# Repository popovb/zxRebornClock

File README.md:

# ИНСТРУКЦИЯ ПО СБОРКЕ И ЗАПУСКУ

## Повышайка на 200 В

Запаиваем следующие элементы: `J1, U3, C8, R55, C9, L1, D8, C11, D7, Q12, R56, Q11, C10, R57, R58`.
Подключаем 12 В. На С11 долно быть около 200 В. Если есть, переходим к следующему шагу.

## Понижайка на 3.3 В

Запаиваем следующие элементы: `D6, C2, U2, C4, C5, R1, D1`. Подключаем 12 В. На C4 должно быть
3.3 В и горит D1. Если есть, переходим к следующему шагу.

## Микроконтроллер

Запаиваем: `U1, C1, J2, U4, R12-R15, D2-D5, Sw2-Sw6, R29-R33, R53, R54, J4`.

Идём сюда https://github.com/ch32-rs/wchisp/releases/tag/v0.3.0 и берём прошиватор
под нужную платформу. Как минимум работает в Debian и Windows 10.

Плата обесточена. Зажимаем кнопку Download, подрубаем usb кабель к компу, отпускаем кнопку и
у нас несколько секунд, чтобы запустить прошиватор.

Для начала можно дать команду вывода информации чипа: `wchisp info`.

Если заработало, то можно прошить `blink.hex` из раздела релизов. Команда `wchisp flash blink.hex`. Будут
мигать светодиоды D2-D5.

Если всё работает -- прошиваем боевую прошивку: `zxRebornClock.hex`.

## Конфигурирование

Питание 12 В и USB выключены. Зажимаем кнопку F и подаём питание 12 В. Загорается зелёный
светодиод -- контроллер перешёл в режим конфигурирования.

Подключаем к J4 USB-Uart переходник и подключаем его к компьютеру.

Из раздела релизов берём программу конфигуратор `zxrc_configurator.win64.exe` или
`zxrc_configurator_lin64` (проверял в Windows 10 и Debian). Запускаем,
выбираем ком-порт и отвечаем на вопросы. В конце будет выдано подтверждение успеха
конфигурирования.

## Дальше

Запаиваем всё остальное. Должно всё заработать.

## Если не заработало?

Тогда идём сюда и спрашиваем https://t.me/zxRebornClock

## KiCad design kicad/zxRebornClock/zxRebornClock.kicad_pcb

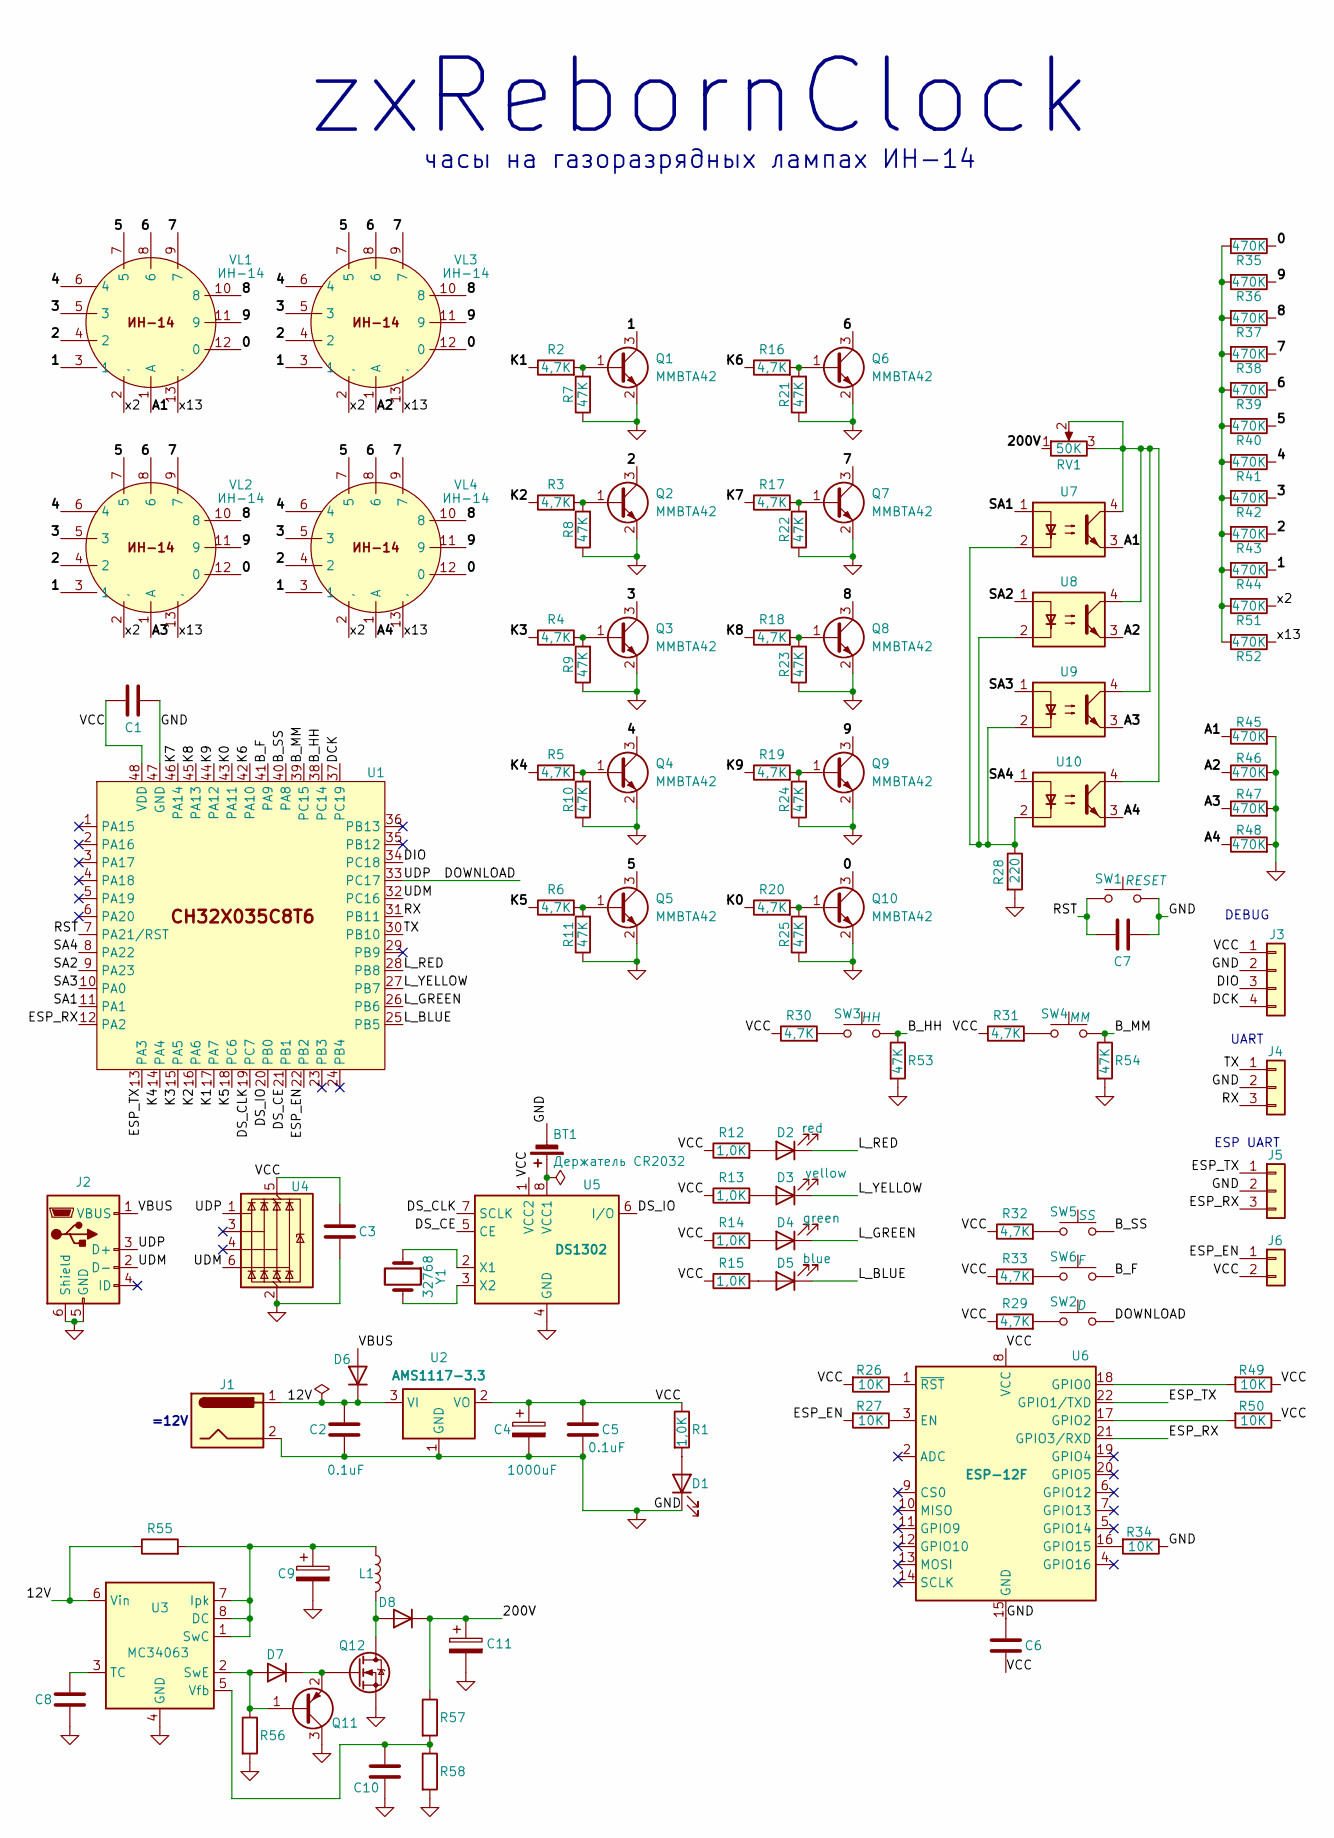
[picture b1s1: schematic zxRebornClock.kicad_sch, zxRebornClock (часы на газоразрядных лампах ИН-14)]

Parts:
BT1: Держатель CR2032; BatteryHolder_MYOUNG_BS-07-A1BJ001_CR2032
C1, C3, C6, C7: 0,1uF; C_0805_2012Metric_Pad1.18x1.45mm_HandSolder
C2, C5: 0.1uF; C_0805_2012Metric_Pad1.18x1.45mm_HandSolder
C4: 1000uF; CP_Radial_D8.0mm_P3.50mm
C8: 2200pF; C_0805_2012Metric_Pad1.18x1.45mm_HandSolder
C9: 220uF; CP_Radial_D6.3mm_P2.50mm
C10: 0.01uF; C_0805_2012Metric_Pad1.18x1.45mm_HandSolder
C11: 2.2uF; CP_Radial_D6.3mm_P2.50mm
D1: white; LED_0805_2012Metric_Pad1.15x1.40mm_HandSolder
D2: red; LED_0805_2012Metric_Pad1.15x1.40mm_HandSolder
D3: yellow; LED_0805_2012Metric_Pad1.15x1.40mm_HandSolder
D4: green; LED_0805_2012Metric_Pad1.15x1.40mm_HandSolder
D5: blue; LED_0805_2012Metric_Pad1.15x1.40mm_HandSolder
D6, D8: US1G; D_SMA
D7: LL4148; D_MiniMELF
J1: Jack DC; BarrelJack_Horizontal
J2: MicroUSB type B розетка; USB_Micro-B_Molex-105017-0001
J3: Гребёнка 1x4x2.54; PinHeader_1x04_P2.54mm_Vertical
J4, J5: Гребёнка 1x3x2.54; PinHeader_1x03_P2.54mm_Vertical
J6: Гребёнка 1x2x2.54; PinHeader_1x02_P2.54mm_Vertical
L1: 100uH; L_D8mm_P3mm
Q1, Q2, Q3, Q4, Q5, Q6, Q7, Q8, Q9, Q10: MMBTA42; SOT-23
Q11: MMBTA56; SOT-23
Q12: IRF740; TO-220-3_Vertical
R1, R12, R13, R14, R15: 1,0K; R_0805_2012Metric_Pad1.20x1.40mm_HandSolder
R2, R3, R4, R5, R6, R16, R17, R18, R19, R20, R29, R30, R31, R32, R33: 4,7K; R_0805_2012Metric_Pad1.20x1.40mm_HandSolder
R7, R8, R9, R10, R11, R21, R22, R23, R24, R25, R53, R54: 47K; R_0805_2012Metric_Pad1.20x1.40mm_HandSolder
R26, R27, R34, R49, R50: 10K; R_0805_2012Metric_Pad1.20x1.40mm_HandSolder
R28: 220; R_0805_2012Metric_Pad1.20x1.40mm_HandSolder
R35, R36, R37, R38, R39, R40, R41, R42, R43, R44, R45, R46, R47, R48, R51, R52: 470K; R_0805_2012Metric_Pad1.20x1.40mm_HandSolder
R55: 0.33; R_0805_2012Metric_Pad1.20x1.40mm_HandSolder
R56: 1K; R_0805_2012Metric_Pad1.20x1.40mm_HandSolder
R57: 470K 1%; R_Axial_DIN0207_L6.3mm_D2.5mm_P7.62mm_Horizontal
R58: 3K 1%; R_Axial_DIN0207_L6.3mm_D2.5mm_P7.62mm_Horizontal
RV1: 50K; TRIM_3362P-1-103
SW1: RESET; SW_SPST_CK_RS282G05A3
SW2: D; SW_SPST_CK_RS282G05A3
SW3: HH; SW_PUSH_6mm_H9.5mm
SW4: MM; SW_PUSH_6mm_H9.5mm
SW5: SS; SW_PUSH_6mm_H9.5mm
SW6: F; SW_PUSH_6mm_H9.5mm
U1: CH32X035C8T6; LQFP-48_7x7mm_P0.5mm
U2: AMS1117-3.3; SOT-223-3_TabPin2
U3: MC34063; SOIC-8_3.9x4.9mm_P1.27mm
U4: USBLC6-4SC6; SOT-23-6
U5: DS1302; SO-8_3.9x4.9mm_P1.27mm
U6: ESP-12F; ESP-12E
U7, U8, U9, U10: TLP627; DIP-4_W7.62mm
VL1, VL2, VL3, VL4: ИН-14
Y1: 32768; Crystal_C38-LF_D3.0mm_L8.0mm_Horizontal

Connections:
/0: Q10.3 (C), R35.1, VL1.12 (0), VL2.12 (0), VL3.12 (0), VL4.12 (0)
/1: Q1.3 (C), R44.1, VL1.3 (1), VL2.3 (1), VL3.3 (1), VL4.3 (1)
/2: Q2.3 (C), R43.1, VL1.4 (2), VL2.4 (2), VL3.4 (2), VL4.4 (2)
/3: Q3.3 (C), R42.1, VL1.5 (3), VL2.5 (3), VL3.5 (3), VL4.5 (3)
/4: Q4.3 (C), R41.1, VL1.6 (4), VL2.6 (4), VL3.6 (4), VL4.6 (4)
/5: Q5.3 (C), R40.1, VL1.7 (5), VL2.7 (5), VL3.7 (5), VL4.7 (5)
/6: Q6.3 (C), R39.1, VL1.8 (6), VL2.8 (6), VL3.8 (6), VL4.8 (6)
/7: Q7.3 (C), R38.1, VL1.9 (7), VL2.9 (7), VL3.9 (7), VL4.9 (7)
/8: Q8.3 (C), R37.1, VL1.10 (8), VL2.10 (8), VL3.10 (8), VL4.10 (8)
/9: Q9.3 (C), R36.1, VL1.11 (9), VL2.11 (9), VL3.11 (9), VL4.11 (9)
/12V: C2.1, D6.1 (K), J1.1, R55.1, U2.3 (VI), U3.6 (Vin)
/200V: C11.1, D8.1 (K), R57.1, RV1.1
/A1: R45.1, U7.3, VL1.1 (A)
/A2: R46.1, U8.3, VL3.1 (A)
/A3: R47.1, U9.3, VL2.1 (A)
/A4: R48.1, U10.3, VL4.1 (A)
/B_F: SW6.2, U1.41 (PA9)
/B_HH: R53.1, SW3.2, U1.38 (PC14)
/B_MM: R54.1, SW4.2, U1.39 (PC15)
/B_SS: SW5.2, U1.40 (PA8)
/DCK: J3.4, U1.37 (PC19)
/DIO: J3.3, U1.34 (PC18)
/DOWNLOAD: J2.3 (D+), SW2.2, U1.33 (PC17), U4.1 (I/O1)
/DS_CE: U1.21 (PB1), U5.5 (CE)
/DS_CLK: U1.19 (PC7), U5.7 (SCLK)
/DS_IO: U1.20 (PB0), U5.6 (I/O)
/ESP_EN: J6.1, R27.2, U1.22 (PB2)
/ESP_RX: J5.3, U1.12 (PA2), U6.21 (GPIO3/RXD)
/ESP_TX: J5.1, U1.13 (PA3), U6.22 (GPIO1/TXD)
/K0: R20.1, U1.43 (PA11)
/K1: R2.1, U1.17 (PA7)
/K2: R3.1, U1.16 (PA6)
/K3: R4.1, U1.15 (PA5)
/K4: R5.1, U1.14 (PA4)
/K5: R6.1, U1.18 (PC6)
/K6: R16.1, U1.42 (PA10)
/K7: R17.1, U1.46 (PA14)
/K8: R18.1, U1.45 (PA13)
/K9: R19.1, U1.44 (PA12)
/L_BLUE: D5.1 (K), U1.25 (PB5)
/L_GREEN: D4.1 (K), U1.26 (PB6)
/L_RED: D2.1 (K), U1.28 (PB8)
/L_YELLOW: D3.1 (K), U1.27 (PB7)
/RST: C7.1, SW1.1, U1.7 (PA21/RST)
/RX: J4.3, U1.31 (PB11)
/SA1: U1.11 (PA1), U7.1
/SA2: U1.9 (PA23), U8.1
/SA3: U1.10 (PA0), U9.1
/SA4: U1.8 (PA22), U10.1
/TX: J4.1, U1.30 (PB10)
/UDM: J2.2 (D-), U1.32 (PC16), U4.6 (I/O4)
/VBUS: D6.2 (A), J2.1 (VBUS)
/VCC: C1.2, C3.1, C4.1, C5.1, C6.2, J3.1, J6.2, R1.1, R12.1, R13.1, R14.1, R15.1, R26.2, R29.1, R30.1, R31.1, R32.1, R33.1, R49.1, R50.1, U1.48 (VDD), U2.2 (VO), U4.5 (VBUS), U5.1 (VCC2), U6.8 (VCC)
/x2: R51.1, VL1.2 (,), VL2.2 (,), VL3.2 (,), VL4.2 (,)
/x13: R52.1, VL1.13 (,), VL2.13 (,), VL3.13 (,), VL4.13 (,)
GND: BT1.2 (-), C1.1, C2.2, C3.2, C4.2, C5.2, C6.1, C7.2, C8.2, C9.2, C10.2, C11.2, D1.1 (K), J1.2, J2.5 (GND), J2.6 (Shield), J3.2, J4.2, J5.2, Q1.2 (E), Q2.2 (E), Q3.2 (E), Q4.2 (E), Q5.2 (E), Q6.2 (E), Q7.2 (E), Q8.2 (E), Q9.2 (E), Q10.2 (E), Q11.3 (C), Q12.3 (S), R7.1, R8.1, R9.1, R10.1, R11.1, R21.1, R22.1, R23.1, R24.1, R25.1, R28.2, R34.1, R45.2, R46.2, R47.2, R48.2, R53.2, R54.2, R56.2, R58.2, SW1.2, U1.47 (GND), U2.1 (GND), U3.4 (GND), U4.2 (GND), U5.4 (GND), U6.15 (GND)
unnamed: BT1.1 (+), U5.8 (VCC1)
unnamed: D1.2 (A), R1.2
unnamed: D2.2 (A), R12.2
unnamed: D3.2 (A), R13.2
unnamed: D4.2 (A), R14.2
unnamed: D5.2 (A), R15.2
unnamed: D7.2 (A), Q11.1 (B), R56.1, U3.2 (SwE)
unnamed: D7.1 (K), Q11.2 (E), Q12.1 (G)
unnamed: D8.2 (A), L1.2, Q12.2 (D)
unnamed: Q1.1 (B), R2.2, R7.2
unnamed: Q2.1 (B), R3.2, R8.2
unnamed: Q3.1 (B), R4.2, R9.2
unnamed: Q4.1 (B), R5.2, R10.2
unnamed: Q5.1 (B), R6.2, R11.2
unnamed: Q6.1 (B), R16.2, R21.2
unnamed: Q7.1 (B), R17.2, R22.2
unnamed: Q8.1 (B), R18.2, R23.2
unnamed: Q9.1 (B), R19.2, R24.2
unnamed: Q10.1 (B), R20.2, R25.2
unnamed: R28.1, U7.2, U8.2, U9.2, U10.2
unnamed: R29.2, SW2.1
unnamed: R30.2, SW3.1
unnamed: R31.2, SW4.1
unnamed: R32.2, SW5.1
unnamed: R33.2, SW6.1
unnamed: R35.2, R36.2, R37.2, R38.2, R39.2, R40.2, R41.2, R42.2, R43.2, R44.2, R51.2, R52.2
unnamed: RV1.2, RV1.3, U7.4, U8.4, U9.4, U10.4
unnamed: C9.1, L1.1, R55.2, U3.1 (SwC), U3.7 (Ipk), U3.8 (DC)
unnamed: C8.1, U3.3 (TC)
unnamed: C10.1, R57.2, R58.1, U3.5 (Vfb)
unnamed: U5.2 (X1), Y1.1
unnamed: U5.3 (X2), Y1.2
unnamed: R27.1, U6.3 (EN)
unnamed: R49.2, U6.18 (GPIO0)
unnamed: R50.2, U6.17 (GPIO2)
unnamed: R34.2, U6.16 (GPIO15)
unnamed: R26.1, U6.1 (~RST)

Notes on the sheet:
=12V
zxRebornClock
DEBUG
часы на газоразрядных лампах ИН-14
UART
ESP UART

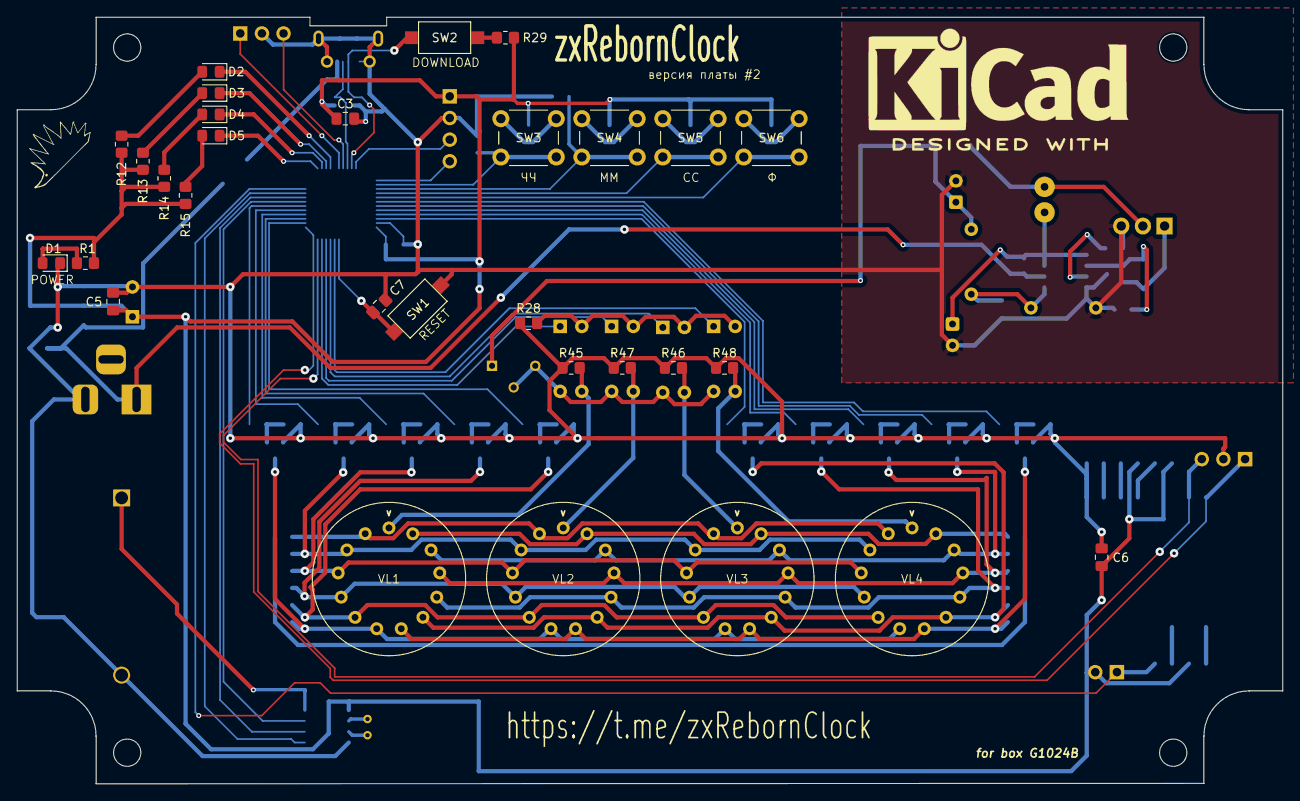
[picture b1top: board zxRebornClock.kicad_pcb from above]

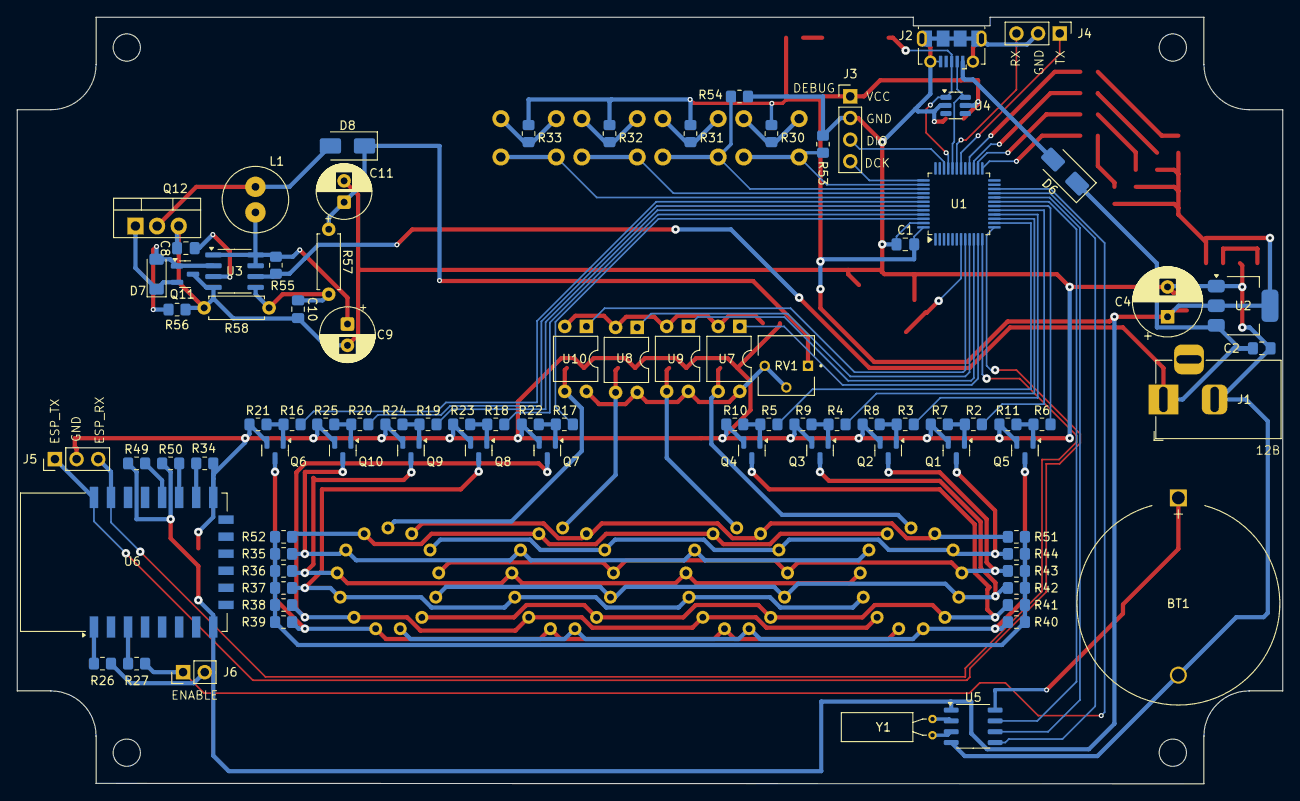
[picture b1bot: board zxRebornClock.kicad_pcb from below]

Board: 2 copper layers, 148.5 x 90.0 mm, 123 parts (89 on the bottom side), 93 nets.

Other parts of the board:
H24, H25, H26, H27: MountingHole; MountingHole_3.2mm_M3

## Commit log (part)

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2025-02-26 work in progress
2025-02-26 fix cathode connect
2025-02-27 fix reset
2025-02-28 add datasheet for USBLC6-4
2025-02-28 add datasheet for USBLC6-4SC6 TECH PUB
2025-02-28 fix schema
2025-02-28 fix ESD
2025-02-28 fix debug connector
2025-02-28 fix leds
2025-02-28 first board iteration is completed
2025-02-28 some fixes
2025-02-28 fix front silk
2025-02-28 fix back silk
2025-02-28 add logos
2025-02-28 add logo
2025-02-28 add pictures
2025-02-28 add gerbers
2025-04-03 ibom: work in progress
2025-04-03 fix pcb
2025-04-06 fix pdf schema
2025-04-06 fix kicad/.gitignore
2025-04-06 remove prl
2025-04-21 ibom is completed
2025-04-22 add LedColor
2025-04-22 add test
2025-04-22 fix McuNetConfig for LedBlock
2025-04-22 fix Configurator
2025-04-22 add impl for ctor for LedBlock
2025-04-22 add impl for LedBlock::init
2025-04-22 add LedTaskMode
2025-04-22 begin proto for LedTaskTime
2025-04-22 add impl for ctor for LedTaskTime
2025-04-22 fix LedTaskMode
2025-04-22 begin proto for LedTask
2025-04-22 add impl for ctor for LedTask
2025-04-22 add proto for LedBlockControl
2025-04-23 begin proto for DisplayTime
2025-04-23 add impl for ctor for DisplayTime
2025-04-23 fix Tubes
2025-04-23 fix main
2025-04-23 add impl for Tubes::calc_iters_per_second
2025-04-23 fix DisplayTime
2025-04-23 fix proto for DisplayTime
2025-04-23 fix impl for ctor for DisplayTime
2025-04-23 remove unused code
2025-04-23 fix test
2025-04-23 add impl for ctor for LedBlockControl
2025-04-23 fix proto for LedBlockControl
2025-04-23 add impl for LedBlockControl::poll
2025-04-23 add impl for LedTask::operator bool
2025-04-23 fix proto for LedTask
2025-04-23 add impl for LedBlockControl::poll_start
2025-04-23 add impl for LedBlockControl::poll_continue
2025-04-23 add impl for Led::operator bool
2025-04-24 add impl for LedBlockControl::poll_continue_up
2025-04-24 add impl for LedBlockControl::poll_continue_down
2025-04-24 refactoring
2025-04-24 add impl for LedBlockControl::set
2025-04-24 fix McuNet
2025-04-24 fix McuNetConfig
2025-04-24 add new blink
2025-05-08 add impl for DisplayTime::display
2025-05-08 add impl for DisplayTime::blank
2025-05-08 fix ockControl:: poll_continue_up, poll_continue_down
2025-05-08 add new main
2025-05-08 add impl for Rtc::set
2025-05-08 add impl for Time::get_hour
2025-05-08 add impl for Time::get_minute
2025-05-08 cleanup
2025-05-08 fix tests
2025-05-09 fix hardware error
2025-05-09 fix DelayerNop
2025-05-09 add impl for Tubes::get_times
2025-05-29 begin conf for buttons ports
2025-05-29 add impl for Configurator::init_button
2025-05-29 add impl for Mcu::init(const ButtonConf&)
2025-05-29 add impl for ctor for ButtonPinConf
2025-05-29 add impl for ctor for ButtonConf
2025-05-29 add impl for ctor for PortPinConf
2025-05-29 fix CMakeLists.txt
2025-05-29 add impl for Mcu::get(const ButtonConf&)
2025-05-29 add impl for Button
2025-05-29 begin proto for Key
2025-05-29 add impl for ctor for Key
2025-05-29 add impl for Key::poll
2025-05-29 add impl for Key::poll_up
2025-05-29 add impl for Key::poll_down
2025-05-29 renaming
2025-05-29 add Key::up
2025-05-29 fix Key::up
2025-05-29 add impl for Key::down
2025-05-31 fix Key::down
2025-05-31 fix proto for Key
2025-05-31 begin proto for KeyBlock
2025-05-31 add impl for ctor for KeyBlock
2025-05-31 add impl for ctor for Button
2025-05-31 add impl for KeyBlock::init
2025-05-31 begin proto for KeyBlockEvent
2025-05-31 fix KeyBlock::init
2025-05-31 add impl for Key::set
2025-05-31 add impl for KeyBlock::poll
2025-05-31 begin proto for KeyBlockReactor
2025-05-31 add impl for ctor for KeyBlockReactor
2025-05-31 add impl for KeyBlockReactor::handle
2025-05-31 add impl for KeyBlockReactor::hour
2025-05-31 add impl for KeyBlockReactor::minute
2025-05-31 add impl for KeyBlockReactor::second
2025-05-31 add impl for KeyBlockReactor::func
2025-06-02 fix Configurator::init
2025-06-02 fix Configurator::init_button
2025-06-02 fix Mcu::init
2025-06-02 fix KeyBlockReactor::handle
2025-06-02 fix KeyBlockReactor::hour
2025-06-02 begin proto for Hour
2025-06-02 add impl for ctor for Hour
2025-06-02 add impl for Hour::operator++
2025-06-02 add impl for Rtc::set(const Hour&)
2025-06-02 add impl for Rtc::set_hour
2025-06-02 add impl for Hour::get
2025-06-02 fix KeyBlockReactor::minute
2025-06-02 add impl for Minute
2025-06-02 add impl for Rtc::set(const Minute&)
2025-06-14 add proto for RedLed
2025-06-14 add impl for ctor for RedLed
2025-06-14 add impl for RedLed::on
2025-06-14 add impl for RedLed::off
2025-06-14 add impl for ctor for Led
2025-06-14 fix RedLed::init
2025-06-14 add impl for ctor for SimpleLed
2025-06-14 add impl for SimpleLed::off
2025-06-14 add impl for SimpleLed::init
2025-06-14 add proto for BlueLed
2025-06-14 add impl for ctor for BlueLed
2025-06-14 add impl for Configurator::init_tx_for_esp
2025-06-14 add impl for Configurator::init_rx_for_esp
2025-06-14 add impl for ctor for cmake
2025-06-14 add impl for Esp12f::init_pin
2025-06-14 add dumb for Esp12f::init_uart
2025-06-14 add impl for Esp12f::enable
2025-06-14 add impl for Esp12f::disable
2025-06-14 add impl for Esp12f::init_uart
2025-06-14 add impl for Esp12f::send
2025-06-14 add impl for Esp12f::receive
2025-06-14 add impl for EspReceiveBuffer::clean
2025-06-15 fix Usart:: send, receive
2025-06-15 receive success
2025-06-21 remove comments
2025-06-21 add impl for Esp12f::wait_sending
2025-06-21 add impl for Uart::tx_not_empty
2025-06-21 add impl for Usart::tx_not_empty
2025-06-21 add impl for Esp12f::receive_one
2025-06-21 add impl for EspReceiveBuffer::completed
2025-06-21 fix proto for EspReceiveBuffer
2025-06-21 add impl for EspReceiveBuffer::get
2025-06-21 add impl for EspReceiveBuffer::ok
2025-06-21 begin proto for InternetTime
2025-06-21 add impl for ctor for InternetTime
2025-06-21 add impl for InternetTime::test
2025-06-21 add impl for ctor for Time
2025-06-21 add impl for Rtc::set_w_second
2025-06-21 add impl for Time::get_second
2025-06-21 add impl for Rtc::set_second
2025-06-21 fix proto for InternetTime
2025-06-21 add impl for ctor for SecondsCounter
2025-06-21 add impl for InternetTime::hour
2025-06-21 add impl for InternetTime::second
2025-06-21 add impl for InternetTime::minute
2025-06-21 begin impl for InternetTime::poll
2025-06-21 fix InternetTime::test
2025-06-21 add impl for InternetTime::poll_enable
2025-06-21 add impl for SecondsCounter::reset
2025-06-21 add impl for SecondsCounter::operator++
2025-06-21 add impl for SecondsCounter::operator bool
2025-06-21 fix InternetTime::poll
2025-06-21 add impl for InternetTime::poll_esp_on
2025-06-22 add impl for InternetTime::has_new_time
2025-06-22 add impl for ctor for TimeStringExtractor
2025-06-22 remove unused tests
2025-06-22 fix for tests
2025-06-22 begin new test
2025-06-22 add impl for TimeStringExtractor::extract_to
2025-06-22 add impl for TimeStringExtractor::find_cr_2
2025-06-22 add impl for TimeStringExtractor::load_year
2025-06-22 add impl for TimeStringExtractor::find_rev
2025-06-22 add impl for TimeStringExtractor::load_second
2025-06-22 add impl for TimeStringExtractor::load_minute
2025-06-22 add impl for TimeStringExtractor::load_hour
2025-06-22 fix TimeStringExtractor::load_hour
2025-06-22 fix TimeStringExtractor::extract_to
2025-06-22 fix TimeStringExtractor::load_minute
2025-06-22 fix KeyBlockReactor::hour, KeyBlockReactor::minute
2025-06-22 fix KeyBlockReactor::second
2025-06-22 fix Rtc::clear_second
2025-06-22 fix proto for KeyBlockReactor
2025-06-22 fix KeyBlockReactor::func
2025-06-22 add impl for InternetTime::forced
2025-06-22 fix InternetTime
2025-06-22 add impl for InternetTime::enable_ntp
2025-06-22 add first work firmware
2025-06-29 remove comment code
2025-06-29 begin set_settings
2025-06-29 add impl for ctor for GreenLed
2025-06-29 add impl for KeyBlock::f_pressed
2025-06-29 add impl for Key::pressed
2025-06-29 fix set_settings
2025-06-29 fix ctor for GreenLed
2025-06-29 add impl for Configurator::init_uart_rx
2025-06-29 add impl for Configurator::init_uart_tx
2025-06-29 fix proto for set_settings
2025-06-29 add proto for UartExchanger
2025-07-12 add impl for ctor for UartExchanger
2025-07-12 add impl for UartExchanger::init_uart
2025-07-12 fix proto for UartExchanger
2025-07-12 add impl for UartExchanger::enable
2025-07-12 add impl for UartExchanger::disable
2025-07-12 add impl for UartExchanger::write
2025-07-12 add impl for UartExchanger::wait_sending
2025-07-12 fix ClockToggler for Uart1
2025-07-12 add impl for UartExchanger::write_buffer
2025-07-13 fix UartExchanger
2025-07-13 begin configurator
2025-07-13 add .gitignore
2025-07-13 add impl for UartExchanger::reset
2025-07-13 add impl for UartExchanger::get
2025-07-19 add proto for FlashSettings
2025-07-19 add impl for ctor for FlashSettings
2025-07-19 add impl for FlashSettings::set_tz
2025-07-19 add impl for FlashSettings::set_ap
2025-07-19 add impl for FlashSettings::set_pass
2025-07-19 add impl for FlashSettings::write
2025-07-19 add impl for FlashSettings::flash_erase
2025-07-19 add impl for FlashSettings::flash_write
2025-07-19 add impl for Mcu::flash_erase
2025-07-19 add impl for Mcu::flash_write
2025-07-19 fix proto for FlashSettings
2025-07-19 add impl for FlashSettings::get_tz
2025-07-19 add impl for FlashSettings::get_ap
2025-07-19 add impl for FlashSettings::get_pass
2025-07-19 add impl for FlashSettings::read
2025-07-20 add impl for InternetTime::start
2025-07-20 add impl for InternetTime::poll_on_mode
2025-07-20 add impl for InternetTime::poll_on_ap
2025-07-20 add impl for EspCommand::build_ap
2025-07-20 add impl for InternetTime::poll_on_ap_pause
2025-07-20 add impl for InternetTime::poll_on_ntp
2025-07-20 add impl for InternetTime::reset_new_time
2025-07-20 add debug info
2025-07-20 add impl for InternetTime::poll_on_ap_test
2025-07-20 add firmware to out
2025-07-25 fix .gitignore
2025-07-25 add module SerialPortFinder
2025-07-25 add module EasySerial
2025-07-26 fix zxrc_configurator.py
2025-07-26 fix find port in win
2025-07-26 add configurator for win64
2025-07-27 add pull-down for B_HH, B_MM
2025-07-27 U5 to SO-5
2025-07-27 new place for leds
2025-07-27 add D6
2025-07-27 add pumper on board
2025-07-27 add new pngs
2025-07-27 add new pdf scheme
2025-07-28 add new gerbers
2025-08-07 begin edit ibom
2025-08-07 fix C for ibom
2025-08-07 fix R for ibom
2025-08-07 fix L, D for ibom
2025-08-07 fix U for ibom
2025-08-07 fix Q for ibom
2025-08-31 add pics
2025-08-31 add LICENSE
2025-08-31 begin README
2025-08-31 fix pdf
2025-08-31 add new inductor
2025-08-31 fix board for new inductor
2025-08-31 fix ibom
2025-11-14 add pumper pics
2025-11-15 fix README.md
